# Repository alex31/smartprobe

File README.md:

# SMARTPROBE Pitot3D device

Smartprobe is an autonomous pitot3d tube that is designed to be mounted on a drone.
It records relative wind speed and angles, stores them on sdcard, and stream data on a serial line.

#### *Disclaimer : software was still in alpha stage when the project development was stopped in fall 2021*

## Installation

### The easy way
use the latest binary found under GitHub Releases

### You really want to compile it ?
### Dependencies installation 

>cross compilation and Perl library for the boardGen.pl tool :

``` shell
sudo apt install build-essential gcc-arm-none-eabi gdb-multiarch \
         default-jre libmodern-perl-Perl \
	 libxml-libxml-Perl libfile-which-Perl \
	 dfu-util
	 
sudo cpan -i String/LCSS.pm
```
> to use bmpflash when flashing with a Black Magic Probe or Criquet Probe
``` shell
sudo usermod -a -G dialout $USER
```
### optional : stm32cubemx install from stmicroelectronics website:
https://www.st.com/en/development-tools/stm32cubemx.html
(boardGen.pl script needs xml MCU description files)
If stm32cubemx is not found, a pregenerated board.h is used, you won't be able to modify pin assignation

### clone of GitHub repository and submodules :
``` shell
git clone --recursive https://github.com/alex31/smartprobe.git
cd smartprobe
git submodule update --init --recursive
```

### build firmware in release mode
``` shell
make clean; make BUILD=SIZE
```

### flash firmware in release mode
In dfu mode :
plug micro-USB cable (no need to power supply)
``` shell
make BUILD=SIZE dfuflash

```
In swd mode :
plug swd cable (need to power supply smartprobe)
``` shell
make BUILD=SIZE flash
``` 

## Usage

### µSD Card
It is mandatory to install a micro sd card :
- SD should be formatted with FAT32 or ExFAT filesystem.
- configuration is read from SD
- wind data is stored on the SD
- reading/writing SD can be done
  - offline : SD must be removed
  - online : plug the smartprobe via USB (with SD installed) on a computer, and it will be shown like a USB storage device

### Connector J3 at the back
The Molex connector at the back contains  :  
- power in : Vin should be between 7 and 20 Volts
- bootloader mode switch (connect pin5 with pin6, then power up the smartprobe)
  -bootloader mode is to be used to flash the firmware in the smartprobe
- USB to mount the sdcard as a USB storage device
- UART which can be used for multiple purposes (choice is made in configuration file)

### Parameters
- firmware parameters are read from the SD at start, in a file named ***smartprobe.conf***
- if a file named smartprobe.conf is not found, it will be created, all the fields set at their default value
- the most accurate and up-to-date definitions (with default and range) for each field can be found in source file  
*source/confParameters.hpp*
- here is a list of parameters (details are missing, confParameters.hpp reading is advised)

|Parameter				|                       Description                   	| default 
|-----------				| --------------------------------------------------  	| -----------
|syslog.filename			| name of the file where system events are logged	|syslog
|sensorslog.filename			| name of the file where sensors data are logged	|sensors
|thread.frequency.d_press		| differential pressure sampling frequency  		|100
|thread.frequency.imu			| IMU sampling frequency 				|100
|thread.frequency.stream_console	| frequency of messages on the console			|10
|thread.frequency.transmit_uart		| frequency of messages on serial link			|100
|ahrs.type				| type of AHRS : raw, headless, or complete		|headless_ahrs
|ahrs.output				| ahrs output format : euler or quaternion		|euler
|uart.mode				| no_used or pprz or nmea_in or ubx_in			|pprz
|pprz.message				| pprz msg to stream data : aeroprobe or smartprobe	|aeroprobe
|uart.baud				| Baud rate of the uart in the range 9600..460800	|115200
|canbus.mode				| not yet implemented					|
|canbus.id				| not yet implemented					|
|sensor.barometer.temperatureBias	| temperature bias of the measured exterior air		|-5
|sensor.barometer.lpf			| barometer clock divider    (see LPS33HW datasheet)	|div2
|sensor.barometer.odr			| barometer output data rate (see LPS33HW datasheet)	|50hz
|sensor.d_press.fetched			| diff pressure param fetched : press or press + temp	|P+T
|sensor.d_press.fetchTempFrequency	| diff pressure temp frequency fetching			|1<<
|sensor.imu.accrate			| imu acc fetching rate (see ICM20600 datasheet)	|1khz_bw99
|sensor.imu.gyrorange			| gyro range [250 .. 2000] degrees per seconds		|250_dps
|sensor.imu.accrange			| acc range [2 .. 16] G					|2g
|sensor.imu.estimationLoopDuration_ms	| ahrs calibration duration [10 .. 4000] milliseconds	|500
|airspeed.rho				| estimated (0) or fixed in the range [0.1 .. 2]	|0(force estimation)
|airspeed.calibration.m11		| transformation matrix	from the			|1.15
|airspeed.calibration.m12		| calibration process					|0
|airspeed.calibration.m13		| default values can be used to verify that		|0
|airspeed.calibration.m14		| the smartprobe roughly works, but should not be	|6
|airspeed.calibration.m15		| used to make actual measures				|6
|airspeed.calibration.m21		| 							|0
|airspeed.calibration.m22		| 							|15
|airspeed.calibration.m23		| 							|0
|airspeed.calibration.m24		| 							|0
|airspeed.calibration.m25		| 							|0
|airspeed.calibration.m31		| 							|0
|airspeed.calibration.m32		| 							|0
|airspeed.calibration.m33		| 							|11
|airspeed.calibration.m34		| 							|0
|airspeed.calibration.m35		|		 					|0
|airspeed.calibration.bias.velocity	|bias on air velocity (from calibration)		|0
|airspeed.calibration.bias.alpha	|bias on alfa angle (from calibration)			|0
|airspeed.calibration.bias.beta 	|bias on beta angle (from calibration)			|0
|led.mode				|status or airspeed					|status
|					|							|

## Calibration
Smartprobe should be calibrated in a wind tunnel before use. The calibration matrix values should then be written in the configuration file instead of the default values.

### Calibration procedure :
...TO BE WRITTEN...

## Development tool
there is a SWD connector on the PCB for connecting a debug probe (Black Magic Probe or STlink V2/V3) which permits debugging with gdb and access to a shell console where errors messages are shown.

## troubleshooting
The led color reflect status of operation (see details below). When error occurs, the error details are logged in the syslog file, on the sdcard, and on debug console if a probe is attached to the internal swd+serial connector.

#### error codes :
- blink green : OK
- blink green and orange : sd card file system is dirty, operation will try to continue, but ultimately, there is a need for filesystem check or reformating
- blink orange : sd card mount has failed
- blink green and white : configuration file error
- blink red : hardware fault detected

..
## Ideas for future developments 
- If external componant (autopilot) stream gps positions and heading, wind in a terrestrial reference frame could be calculated on board
- add USB CDC endoint to the existing USB storage endpoint to output serial console shell via USB
- stream UAVCAN messages on the CAN 2.0B interface

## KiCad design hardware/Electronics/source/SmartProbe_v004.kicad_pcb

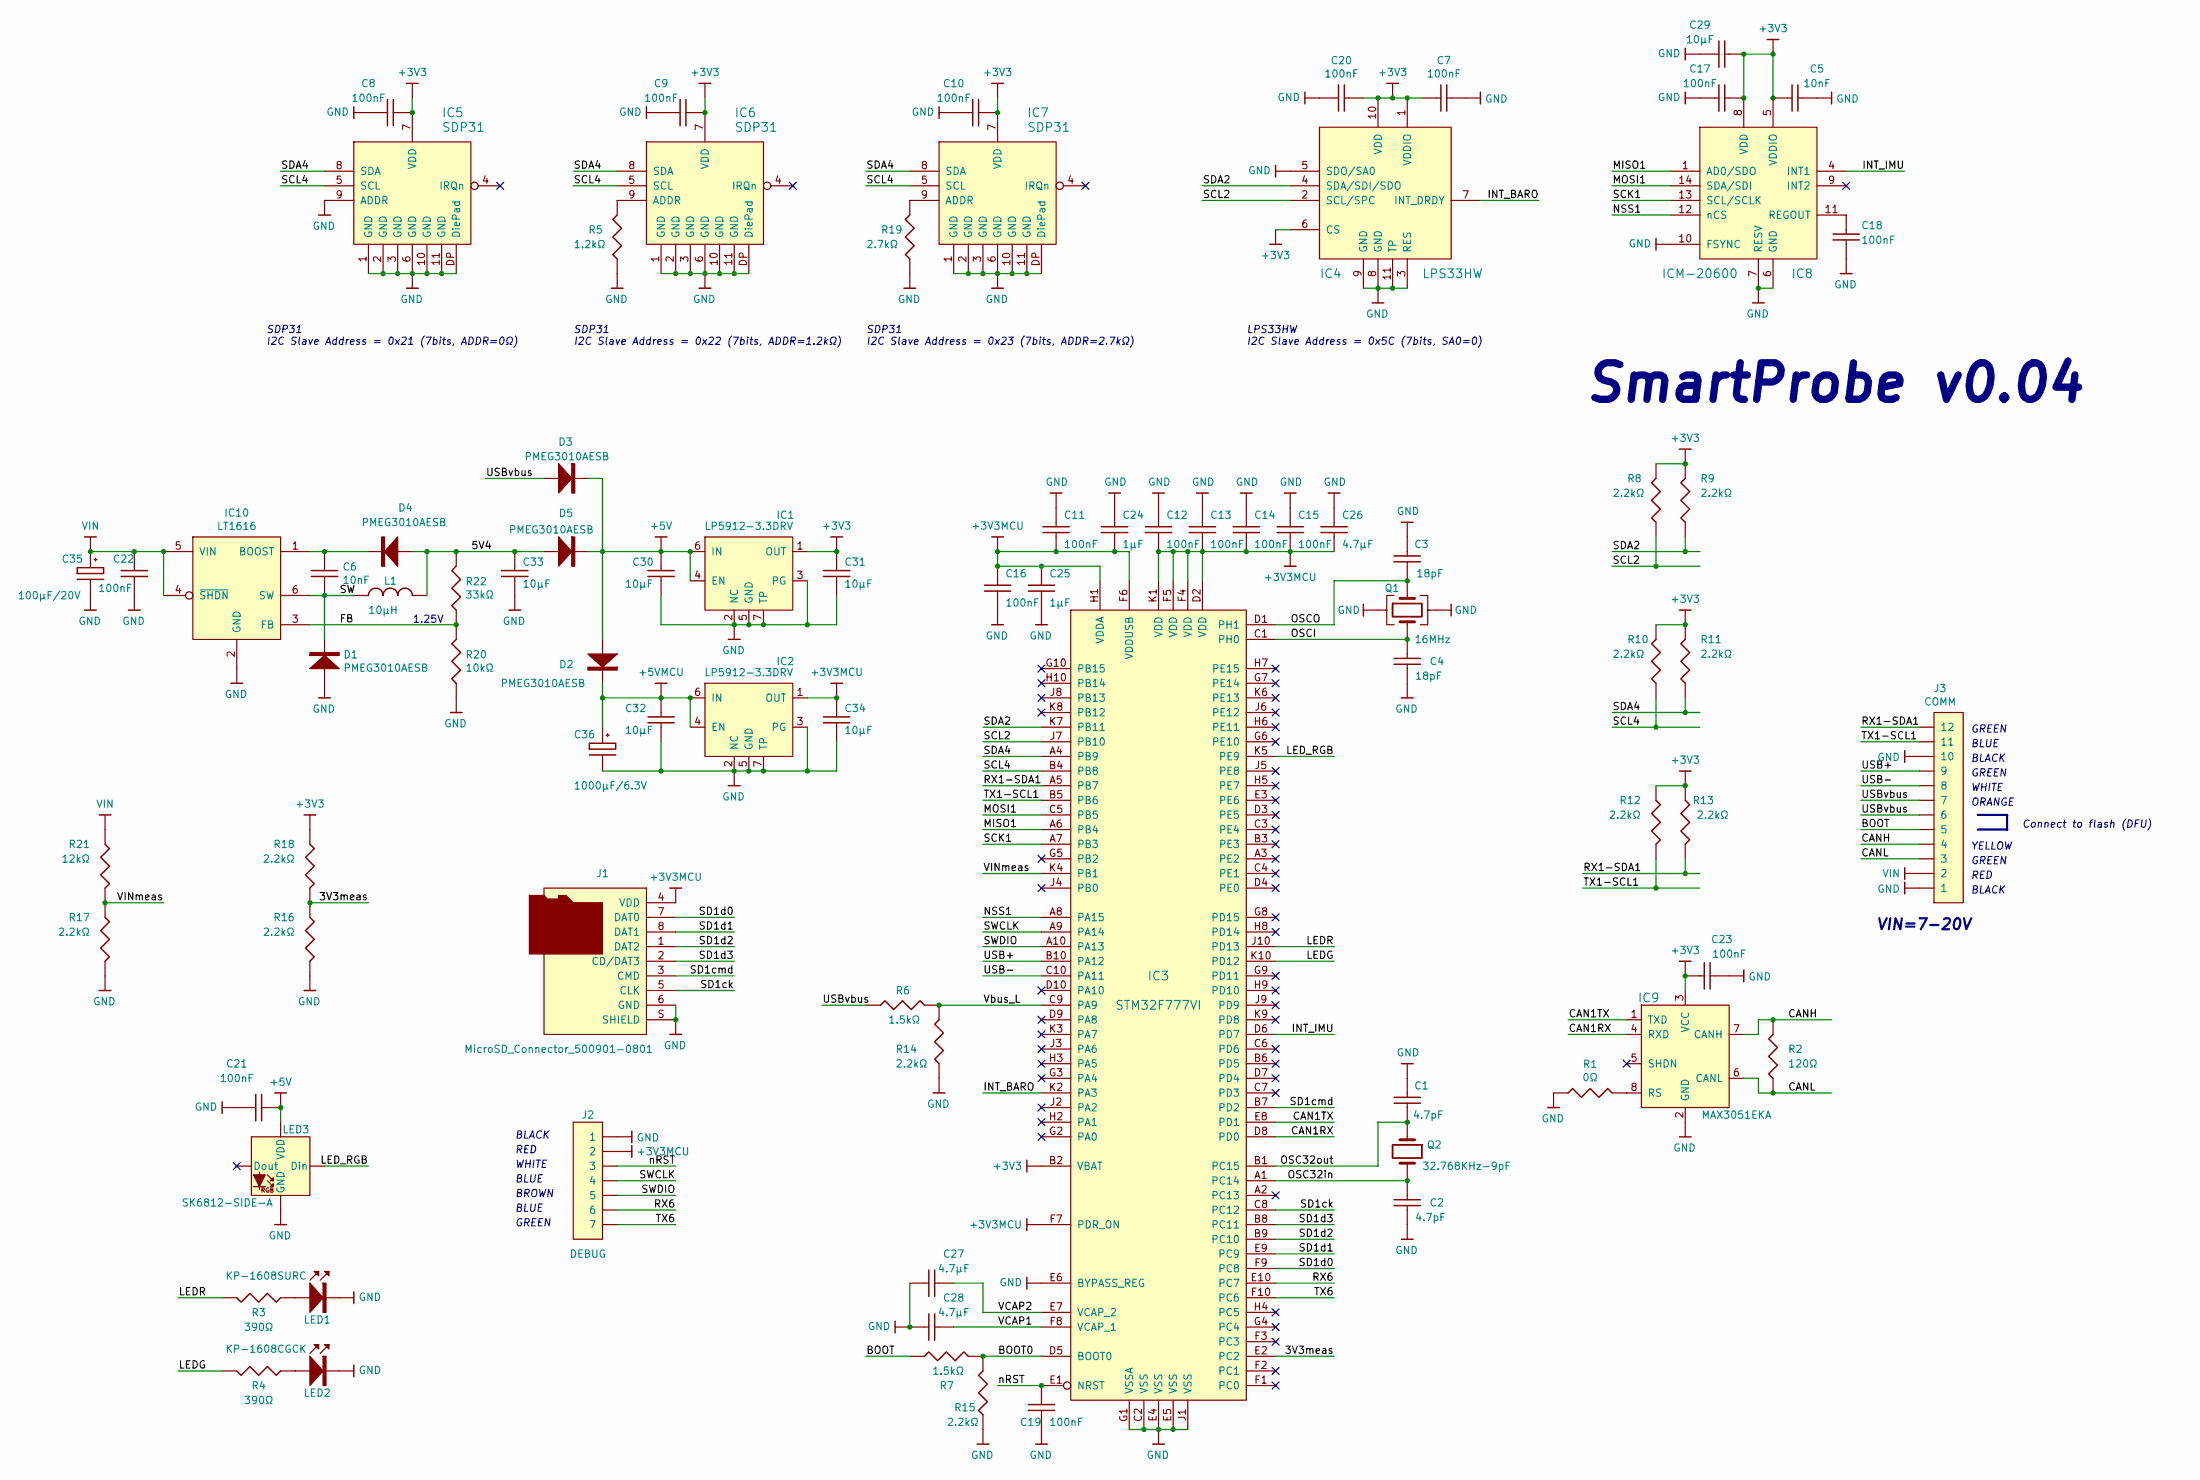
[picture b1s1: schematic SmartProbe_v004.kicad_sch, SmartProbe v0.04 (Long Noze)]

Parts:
C1, C2: 4.7pF; C_0402
C3, C4: 18pF; C_0402
C5, C6: 10nF; C_0402
C7, C8, C9, C10, C11, C12, C13, C14, C15, C16, C17, C18, C19, C20, C21, C22, C23: 100nF; C_0402
C24, C25: 1µF; C_0402
C26, C27, C28: 4.7µF; C_0402
C29, C30, C31, C32, C33, C34: 10µF; C_0603
C35: 100µF/20V; EIA_7343-31
C36: 1000µF/6.3V; EIA_7360-38
D1, D2, D3, D4, D5: PMEG3010AESB
IC1, IC2: LP5912-3.3DRV; LP5912DRV
IC3: STM32F777VI
IC4: LPS33HW
IC5, IC6, IC7: SDP31
IC8: ICM-20600
IC9: MAX3051EKA
IC10: LT1616
J1: MicroSD_Connector_500901-0801; MicroSD_500901-0801
J2: DEBUG; PicoBlade_53261-0771
J3: COMM; PicoBlade_53048-1210
L1: 10µH; VLCF4020T
LED1: KP-1608SURC
LED2: KP-1608CGCK
LED3: SK6812-SIDE-A
Q1: 16MHz; Crystal_8Z
Q2: 32.768KHz-9pF; Crystal_FC-135
R1: 0Ω; R_0402
R2: 120Ω; R_0402
R3, R4: 390Ω; R_0402
R5: 1.2kΩ; R_0402
R6, R7: 1.5kΩ; R_0402
R8, R9, R10, R11, R12, R13, R14, R15, R16, R17, R18: 2.2kΩ; R_0402
R19: 2.7kΩ; R_0402
R20: 10kΩ; R_0402
R21: 12kΩ; R_0402
R22: 33kΩ; R_0402

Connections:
+3V3: C5.2, C7.2, C8.1, C9.1, C10.1, C17.1, C20.1, C23.2, C29.1, C31.1, IC1.1 (OUT), IC3.B2 (VBAT), IC4.1 (VDDIO), IC4.6 (CS), IC4.10 (VDD), IC5.7 (VDD), IC6.7 (VDD), IC7.7 (VDD), IC8.5 (VDDIO), IC8.8 (VDD), IC9.3 (VCC), R8.1, R9.1, R10.1, R11.1, R12.1, R13.1, R18.1
+3V3MCU: C11.2, C12.2, C13.2, C14.2, C15.2, C16.1, C24.2, C25.1, C26.2, C34.1, IC2.1 (OUT), IC3.D2 (VDD), IC3.F4 (VDD), IC3.F5 (VDD), IC3.F6 (VDDUSB), IC3.F7 (PDR_ON), IC3.H1 (VDDA), IC3.K1 (VDD), J1.4 (VDD), J2.2
+5V: C21.1, C30.1, D2.2 (A), D3.1 (K), D5.1 (K), IC1.4 (EN), IC1.6 (IN), LED3.2 (VDD)
+5VMCU: C32.1, C36.1, D2.1 (K), IC2.4 (EN), IC2.6 (IN)
/3V3meas: IC3.E2 (PC2), R16.1, R18.2
/5V4: C33.1, D4.2 (A), D5.2 (A), L1.2, R22.1
/BOOT: J3.5, R7.2
/BOOT0: IC3.D5 (BOOT0), R7.1, R15.1
/CAN1RX: IC3.D8 (PD0), IC9.4 (RXD)
/CAN1TX: IC3.E8 (PD1), IC9.1 (TXD)
/CANH: IC9.7 (CANH), J3.4, R2.1
/CANL: IC9.6 (CANL), J3.3, R2.2
/FB: IC10.3 (FB), R20.1, R22.2
/INT_BARO: IC3.K2 (PA3), IC4.7 (INT_DRDY)
/INT_IMU: IC3.D6 (PD7), IC8.4 (INT1)
/LEDG: IC3.K10 (PD12), R4.1
/LEDR: IC3.J10 (PD13), R3.1
/LED_RGB: IC3.K5 (PE9), LED3.1 (Din)
/MISO1: IC3.A6 (PB4), IC8.1 (AD0/SDO)
/MOSI1: IC3.C5 (PB5), IC8.14 (SDA/SDI)
/NSS1: IC3.A8 (PA15), IC8.12 (nCS)
/OSC32in: C2.2, IC3.A1 (PC14), Q2.2
/OSC32out: C1.2, IC3.B1 (PC15), Q2.1
/OSCI: C4.2, IC3.C1 (PH0), Q1.3
/OSCO: C3.2, IC3.D1 (PH1), Q1.1
/RX1-SDA1: IC3.A5 (PB7), J3.12, R13.2
/RX6: IC3.E10 (PC7), J2.6
/SCK1: IC3.A7 (PB3), IC8.13 (SCL/SCLK)
/SCL2: IC3.J7 (PB10), IC4.2 (SCL/SPC), R8.2
/SCL4: IC3.B4 (PB8), IC5.5 (SCL), IC6.5 (SCL), IC7.5 (SCL), R10.2
/SD1ck: IC3.C8 (PC12), J1.5 (CLK)
/SD1cmd: IC3.B7 (PD2), J1.3 (CMD)
/SD1d0: IC3.F9 (PC8), J1.7 (DAT0)
/SD1d1: IC3.E9 (PC9), J1.8 (DAT1)
/SD1d2: IC3.B9 (PC10), J1.1 (DAT2)
/SD1d3: IC3.B8 (PC11), J1.2 (CD/DAT3)
/SDA2: IC3.K7 (PB11), IC4.4 (SDA/SDI/SDO), R9.2
/SDA4: IC3.A4 (PB9), IC5.8 (SDA), IC6.8 (SDA), IC7.8 (SDA), R11.2
/SW: C6.2, D1.1 (K), IC10.6 (SW), L1.1
/SWCLK: IC3.A9 (PA14), J2.4
/SWDIO: IC3.A10 (PA13), J2.5
/TX1-SCL1: IC3.B5 (PB6), J3.11, R12.2
/TX6: IC3.F10 (PC6), J2.7
/USB+: IC3.B10 (PA12), J3.9
/USB-: IC3.C10 (PA11), J3.8
/USBvbus: D3.2 (A), J3.6, J3.7, R6.2
/VCAP1: C28.1, IC3.F8 (VCAP_1)
/VCAP2: C27.1, IC3.E7 (VCAP_2)
/VINmeas: IC3.K4 (PB1), R17.1, R21.2
/Vbus_L: IC3.C9 (PA9), R6.1, R14.1
/nRST: C19.1, IC3.E1 (NRST), J2.3
GND: C1.1, C2.1, C3.1, C4.1, C5.1, C7.1, C8.2, C9.2, C10.2, C11.1, C12.1, C13.1, C14.1, C15.1, C16.2, C17.2, C18.2, C19.2, C20.2, C21.2, C22.2, C23.1, C24.1, C25.2, C26.1, C27.2, C28.2, C29.2, C30.2, C31.2, C32.2, C33.2, C34.2, C35.2, C36.2, D1.2 (A), IC1.2 (NC), IC1.3 (PG), IC1.5 (GND), IC1.7 (TP), IC2.2 (NC), IC2.3 (PG), IC2.5 (GND), IC2.7 (TP), IC3.C2 (VSS), IC3.E4 (VSS), IC3.E5 (VSS), IC3.E6 (BYPASS_REG), IC3.G1 (VSSA), IC3.J1 (VSS), IC4.3 (RES), IC4.5 (SDO/SA0), IC4.8 (GND), IC4.9 (GND), IC4.11 (TP), IC5.1 (GND), IC5.2 (GND), IC5.3 (GND), IC5.6 (GND), IC5.9 (ADDR), IC5.10 (GND), IC5.11 (GND), IC5.DP (DiePad), IC6.1 (GND), IC6.2 (GND), IC6.3 (GND), IC6.6 (GND), IC6.10 (GND), IC6.11 (GND), IC6.DP (DiePad), IC7.1 (GND), IC7.2 (GND), IC7.3 (GND), IC7.6 (GND), IC7.10 (GND), IC7.11 (GND), IC7.DP (DiePad), IC8.6 (GND), IC8.7 (RESV), IC8.10 (FSYNC), IC9.2 (GND), IC10.2 (GND), J1.6 (GND), J1.S (SHIELD), J2.1, J3.1, J3.10, LED1.1 (K), LED2.1 (K), LED3.4 (GND), Q1.2, Q1.4, R1.2, R5.2, R14.2, R15.2, R16.2, R17.2, R19.2, R20.2
unnamed: C6.1, D4.1 (K), IC10.1 (BOOST)
unnamed: C18.1, IC8.11 (REGOUT)
unnamed: IC6.9 (ADDR), R5.1
unnamed: IC7.9 (ADDR), R19.1
unnamed: IC9.8 (RS), R1.1
unnamed: LED1.2 (A), R3.2
unnamed: LED2.2 (A), R4.2
VIN: C22.1, C35.1, IC10.4 (~SHDN), IC10.5 (VIN), J3.2, R21.1

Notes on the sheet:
GREEN
BLACK
1.25V
ORANGE
BROWN
BLUE
WHITE
SDP31 I2C Slave Address = 0x22 (7bits, ADDR=1.2kΩ)
SDP31 I2C Slave Address = 0x21 (7bits, ADDR=0Ω)
VIN=7-20V
YELLOW
RED
LPS33HW I2C Slave Address = 0x5C (7bits, SA0=0)
SmartProbe v0.04
Connect to flash (DFU)
SDP31 I2C Slave Address = 0x23 (7bits, ADDR=2.7kΩ)

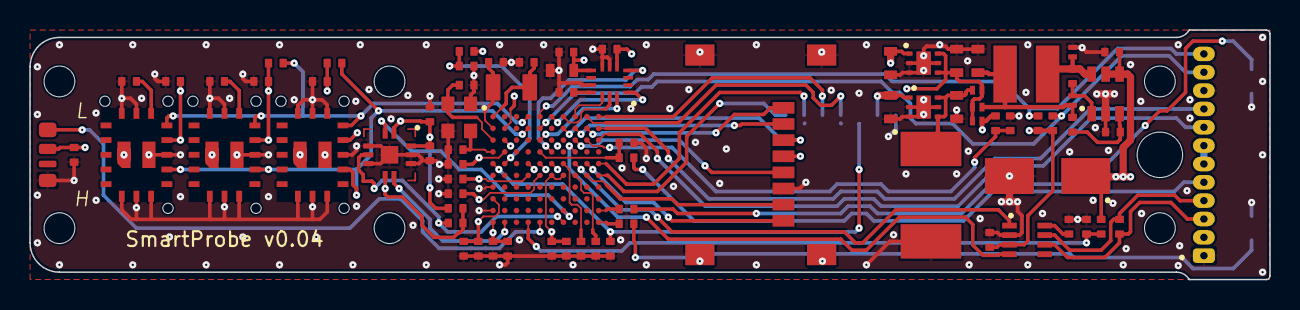
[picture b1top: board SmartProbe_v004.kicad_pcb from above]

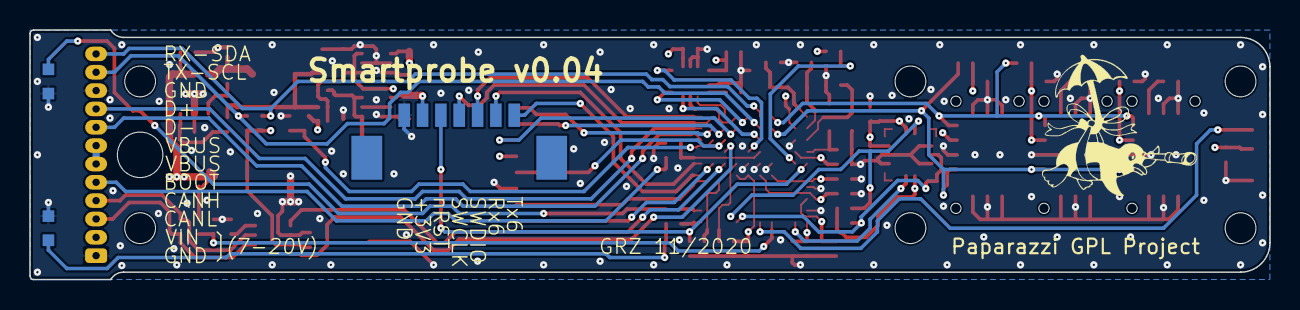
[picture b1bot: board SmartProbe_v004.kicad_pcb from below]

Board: 4 copper layers, 84.5 x 17.0 mm, 82 parts (3 on the bottom side), 60 nets.

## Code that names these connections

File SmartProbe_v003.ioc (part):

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Mcu.Name=STM32F777VIHx
Mcu.Package=TFBGA100
Mcu.UserName=STM32F777VIHx
PA11.GPIOParameters=GPIO_Label
PA11.GPIO_Label=USB-
PA11.Mode=Device_Only
PA11.Signal=USB_OTG_FS_DM
PA12.GPIOParameters=GPIO_Label
PA12.GPIO_Label=USB+
PA12.Mode=Device_Only
PA12.Signal=USB_OTG_FS_DP
PA13.GPIOParameters=GPIO_Label
PA13.GPIO_Label=SWDIO
PA13.Mode=Serial_Wire
PA13.Signal=SYS_JTMS-SWDIO
PA14.GPIOParameters=GPIO_Label
PA14.GPIO_Label=SWCLK
PA14.Mode=Serial_Wire
PA14.Signal=SYS_JTCK-SWCLK
PA15.GPIOParameters=GPIO_Label
PA15.GPIO_Label=NSS1
PA15.Mode=NSS_Signal_Hard_Output
PA15.Signal=SPI1_NSS
PA3.GPIOParameters=GPIO_Label
PA3.GPIO_Label=INT_BARO
PA3.Signal=GPIO_Input
PA9.GPIOParameters=GPIO_Label
PA9.GPIO_Label=Vbus
PA9.Mode=Activate_VBUS
PA9.Signal=USB_OTG_FS_VBUS
PB1.GPIOParameters=GPIO_Label
PB1.GPIO_Label=VINmeas
PB1.Signal=ADCx_IN9
PB10.GPIOParameters=GPIO_Label
PB10.GPIO_Label=SCL2
PB10.Mode=I2C
PB10.Signal=I2C2_SCL
PB11.GPIOParameters=GPIO_Label
PB11.GPIO_Label=SDA2
PB11.Mode=I2C
PB11.Signal=I2C2_SDA
PB3.GPIOParameters=GPIO_Label
PB3.GPIO_Label=SCK1
PB3.Mode=Full_Duplex_Master
PB3.Signal=SPI1_SCK
PB4.GPIOParameters=GPIO_Label
PB4.GPIO_Label=MISO1
PB4.Mode=Full_Duplex_Master
PB4.Signal=SPI1_MISO
PB5.GPIOParameters=GPIO_Label
PB5.GPIO_Label=MOSI1
PB5.Mode=Full_Duplex_Master
PB5.Signal=SPI1_MOSI
PB6.GPIOParameters=GPIO_Label
PB6.GPIO_Label=TX1-SCL1
PB6.Mode=Asynchronous
PB6.Signal=USART1_TX
PB7.GPIOParameters=GPIO_Label
PB7.GPIO_Label=RX1-SDA1
PB7.Mode=Asynchronous
PB7.Signal=USART1_RX
PB8.GPIOParameters=GPIO_Label
PB8.GPIO_Label=SCL4
PB8.Mode=I2C
PB8.Signal=I2C4_SCL
PB9.GPIOParameters=GPIO_Label
PB9.GPIO_Label=SDA4
PB9.Mode=I2C
PB9.Signal=I2C4_SDA
PC10.GPIOParameters=GPIO_Label
PC10.GPIO_Label=SD1d2
PC10.Mode=SD_4_bits_Wide_bus
PC10.Signal=SDMMC1_D2
PC11.GPIOParameters=GPIO_Label
PC11.GPIO_Label=SD1d3
PC11.Mode=SD_4_bits_Wide_bus
PC11.Signal=SDMMC1_D3
PC12.GPIOParameters=GPIO_Label
PC12.GPIO_Label=SD1ck
PC12.Mode=SD_4_bits_Wide_bus
PC12.Signal=SDMMC1_CK
PC14/OSC32_IN.GPIOParameters=GPIO_Label
PC14/OSC32_IN.GPIO_Label=OSC32IN
PC14/OSC32_IN.Mode=LSE-External-Oscillator
PC14/OSC32_IN.Signal=RCC_OSC32_IN
PC15/OSC32_OUT.GPIOParameters=GPIO_Label
PC15/OSC32_OUT.GPIO_Label=OSC32OUT
PC15/OSC32_OUT.Mode=LSE-External-Oscillator
PC15/OSC32_OUT.Signal=RCC_OSC32_OUT
PC2.GPIOParameters=GPIO_Label
PC2.GPIO_Label=_3V3meas
PC2.Signal=ADCx_IN12
PC6.GPIOParameters=GPIO_Label
PC6.GPIO_Label=TX6
PC6.Mode=Asynchronous
PC6.Signal=USART6_TX
PC7.GPIOParameters=GPIO_Label
PC7.GPIO_Label=RX6
PC7.Mode=Asynchronous
PC7.Signal=USART6_RX
PC8.GPIOParameters=GPIO_Label
PC8.GPIO_Label=SD1d0
PC8.Mode=SD_4_bits_Wide_bus
PC8.Signal=SDMMC1_D0
PC9.GPIOParameters=GPIO_Label
PC9.GPIO_Label=SD1d1
PC9.Mode=SD_4_bits_Wide_bus
PC9.Signal=SDMMC1_D1
PD0.GPIOParameters=GPIO_Label
PD0.GPIO_Label=CAN1RX
PD0.Mode=Master
PD0.Signal=CAN1_RX
PD1.GPIOParameters=GPIO_Label
PD1.GPIO_Label=CAN1TTX
PD1.Mode=Master
PD1.Signal=CAN1_TX
PD12.GPIOParameters=GPIO_Label
PD12.GPIO_Label=LEDG
PD12.Signal=GPIO_Output
PD13.GPIOParameters=GPIO_Label
PD13.GPIO_Label=LEDR
PD13.Signal=GPIO_Output
PD2.GPIOParameters=GPIO_Label
PD2.GPIO_Label=SD1cmd
PD2.Mode=SD_4_bits_Wide_bus
PD2.Signal=SDMMC1_CMD
PD7.GPIOParameters=GPIO_Label
PD7.GPIO_Label=INT_IMU
PD7.Signal=GPIO_Input
PE9.GPIOParameters=GPIO_Label
PE9.GPIO_Label=LED_RGB
PE9.Signal=S_TIM1_CH1
PH0/OSC_IN.Mode=HSE-External-Oscillator
PH0/OSC_IN.Signal=RCC_OSC_IN
PH1/OSC_OUT.Mode=HSE-External-Oscillator
PH1/OSC_OUT.Signal=RCC_OSC_OUT
RCC.HSE_VALUE=25000000
board=custom

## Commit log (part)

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2019-10-25 only basic shell in c++
2019-10-25 smartprobe : board.cfg written for specific hardware
2019-10-30 remove globalVar
2019-10-30 modify Makefile to add CTRE, FROZEN and ETL header only libraries
2019-11-05 use fpu
2019-11-08 add fatfs, tlsf
2019-11-15 add sdLog
2019-11-15 add i2cMaster, spi; fix dma streams
2019-11-15 add baro thread
2019-11-15 add and abstaction of a working class
2019-11-16 add join, terminate, and destructor
2019-11-18 fix thread abstaction, before baro using thread abstaction, tested ok on devboardm767
2019-11-18 add missing files
2019-11-19 baro use thread abstraction
2019-11-19 add adc, apply CRTP to worker template class to avoid thread handle sharing
2019-11-19 add imu, not tested
2019-11-20 add sdcard, tested on devboardm767 ok
2019-11-20 all peripherals tested ok on smartprobe
2019-11-21 use reworked sdLog.c whith fixed autoflush period, works ok without dirty bit on few tries. Should be teste more thoroughly
2019-11-21 fix incorrect values of the resistors used in the power supply voltage divider
2019-11-25 add blackboard.hpp
2019-11-25 add blackBoard test files
2019-11-25 baro, adc and differential pressure emit event
2019-11-25 fix main trhead stack size in optimized compilation
2019-11-26 imu also send event, so now all sensors send events
2019-11-26 update todolist
2019-11-26 add usb_storage
2019-11-27 workerClass : avoid virtual inderection in loop using CRTP
2019-11-27 indicate that thread run only once using noreturn kw
2019-11-27 change led1 led2 by led_green led_red
2019-11-27 use syslog instead of debug trace, write git revision and other useful info @ syslog start
2019-11-27 log all sensors data @100 hz on the sdcard
2019-11-27 fix source event : dpif instead of baro
2019-11-27 fix event was sent for each of the 3 dp sensors, but only one event is expected
2019-11-28 add a rough program to display sensors output
2019-11-28 refresh binaries
2019-11-28 clean flow control in main.cpp, simplify shell close command
2019-11-28 fix stopAllPeripherals, called in case of power supply stop. it made chibios chSysHalt, and no sdcard clean close was done
2019-12-03 4.4v threshold for tests before dynamic threshold
2019-12-03 dynamic shutdown threashold voltage (not tested)
2019-12-04 fix app code because of chibios fix #1060 to restore usb_storage; fix VSS initial calculation
2019-12-12 generate binary
2019-12-12 portage from linux to MCU fails because of embedded libc++ limitation : try to switch to etl
2019-12-13 initial portage completed whithout the need to switch to ETL
2019-12-14 read / write conf file code written, not tested
2019-12-14 begin use of conf parameters
2019-12-14 first actual use of conf parameters
2019-12-14 use conf parameter for sensors initialisation parameters
2019-12-17 raise dynamic memory pool size, raise threads stack size, still memory problem with certain level of optimisation, namely -Og
2019-12-17 fix dynamic string possibily of failure
2019-12-17 replace some string_view by std::string to avoid memory corruption
2019-12-17 modity makefile to permit so select build type (DEBUG, SIZE, SPEED) on command line
2019-12-17 remove ETL : F7 don't lack memory, and we need dynamic allocation, so we can use STL for all
2019-12-17 test and reformat syslog messages generated by configuration file reading : tested OK
2019-12-18 print associated alias for default value and syslog message, update todo.txt
2019-12-19 integrate ahrs, still need to log euler angles to sdcard
2019-12-20 log euler angles to sdcard, with a configuration parameter to choose between raw imu and ahrs estimated euler angles
2019-12-21 calculate relative wind vector : big concern about calibration matrix orientation numpy vs eigen
2019-12-21 use eigen operator[] to get vector element instead operator ()
2019-12-21 estimate rho from baro, or use std value given in conf file
2019-12-22 raise d_press to 2khz (need new sdp3x), replace fast inv sqrt by std use of FPU
2019-12-22 test is a line is too long for the internal buffer to avoid a crash
2019-12-22 add parameters for SDP3X : fetch pressure and temperature, temperature getch frequency relative to pressure
2019-12-23 crashes orginin is : newlib's *s*printf class of function are not reentrant (libc one are, so man say it's reentrant) : I commit a temporary fix using newlib _*s*printf_r class of function, but the r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
2019-12-23 add a copy of the configuration file on the sdcard smartprobe.conf, update todo.txt
2019-12-23 revert Makefile debug build to -Og
2019-12-23 add binary with their new name
2019-12-23 fix potential problems : no reentrancy of newlib sprintf, protect (mutex) configuration dictionary access, preallocate std::string
2019-12-23 more precise timestamp when aquisition frequency is over >= 100hz
2019-12-24 fix va_list bug when no trace, fix no serialdatastrem when no trace
2019-12-25 make line parsing more robust : ctre sometime crash, so comment remove is done by strtok prior to regexp matching
2019-12-25 revert to STM32F777VIHx (part in board.cfg)
2020-01-08 make all internal IMU angle be in radian, degree only used for display and ascii log. 3d wind calculus stay in degrees for now
2020-01-08 detect swdio activity, and close cleanly sdcard before entering swdio mode; put fatfs in pedantic mode : will not mount FS with dirty bit neither cluster incoherency
2020-01-08 fix swdio action after deteection
2020-01-22 in the streamed data (low frequency), mean attitude and air vector instead of taking one sample
2020-02-05 display fixes in spGui.pl
2020-02-06 add capacity to send aeroprobe message to pprz via uart (not tested)
2020-02-07 add capacity to get pprz message from uart (not tested)
2020-02-07 launch uart receive thread in main.cpp when mode is PPRZ_IN_OUT
2020-02-07 generate binaries
2020-02-14 emit event on pprz message, implement itow to rtcdate
2020-02-14 change file and class name
2020-02-14 change file and class name (part 2)
2020-02-14 add pprzlink encoder decoder files
2020-02-20 remove warning about wind velocity calculation : tested OK
2020-02-26 still bugs in reading conf files
2020-02-26 add a comment sign (#) after value when generating conf file
2020-02-26 do no run showBB when uart is in link mode
2020-02-27 add warning and checks at compilation, modify sources according to new rules
2020-02-27 fix serial driver initialisation
2020-02-27 remove test code for ppzr link
2020-02-28 fix method to wait for uart initialisation
2020-02-28 add code to sync RTC with GPS (not tested)
2020-03-16 add gps nmea input (not finished, lacks pubx 00
2020-03-18 create unit test for nmeaFrame modification
2020-03-19 add and test nmea pubx,yy message reception, tested OK
2020-03-19 remove binding to GGA and VTG nmea message which are no more needed when using PUBX,00
2020-03-19 fix lla to utm conversion
2020-03-26 UBX : discard faster non ubx or non topic message, syslog quantity of discard garbage
2020-03-26 add configuration value : canbus id in prevision of installing many SP on a plane
2020-03-26 fix uwb swallow bug which lead to read 0 bytes on a channel (chibios trapped error)
2020-03-26 add schematics of V003 version of the board
2020-03-27 update todo
2020-03-27 use new pprzlink api with user data
2020-03-30 fix ubx event bug
2020-03-30 sensorlog (TSV format) gps data if avalaible
2020-03-30 add etl profile since we use it again
2020-04-01 remove stuff in mail
2020-04-01 trace uart speed is not anymore in configuration file, add non compound statement macro since the compund one trigger a strange bug
2020-04-01 fix order of initialisation : get log name from configuration file
2020-04-02 fix chronology problem at start, move constants to hardwareConf.hpp
2020-04-02 simplify main, enable MPU based stack overflow check
2020-04-02 fix a very serious bug in dynamic memory management : operateur new and delete was not redefinded in all copilation units
2020-04-08 add binary log option and tool to convert offline binary logs to tsv logs
2020-04-08 add 3d rendering of smartprobe
2020-04-15 raise main thread stack size
2020-04-27 we do not use pwmd9
2020-05-11 make g++10 happy
2020-06-02 fix printf format errors
2020-06-09 begin replacement of sdLog library by sdLiteLog (not finished)
2020-06-12 sdLiteLog finish replacement of sdLog library by sdLiteLog, tested, seems OK, need more tests
2020-07-01 use C++ fmt library instead of C stdio sprintf : speed gain of 60%
2020-07-01 use of sdLiteLog : buffer size is centralised in hardwareConf.hpp
2020-07-01 fix typo in logical test
2020-09-02 portage to v003 : led in the noose, voltage from battery no from 5V regulator
2020-09-03 port to chibios 20.03
2020-09-03 add some submodules, needs a lot more
2020-09-08 fix µsecond calculus truncated to 32 bits : was wrapping after 1 hour and 10 minutes
2020-09-08 time in binary and text log are now expressed in seconds, not milliseconds
2020-09-08 fix hard hangs at first start after sdcard reformat
2020-09-09 add LTO in Makefile
2020-09-09 power supply is not 5V anymore, so change the label
2020-09-09 launch showBB thread only whenh TRACE is defined
2020-09-17 sample 4 adc channels
2020-09-17 repair wronf git command
2020-09-17 do no track generated file board.h
2020-09-18 smartled : add a starting state where we cycle over Hue values
2020-09-18 add led code for swdio mode, detect and wait
2020-09-18 periodicly check thread stack occupancy, internal voltage, core temp and log abnormal values
2020-09-22 use INT1 pin of IMU TDK20600 to trigger acquisition
2020-09-23 put eigen in a submodule
2020-09-23 put all depencies as submodules
2020-09-23 add file
2020-09-23 add README.md
2020-09-23 add Makefile entry to flash in dfu mode
2020-09-23 fix typos in README.md
2020-09-23 begin to fix bad behaviour chan compiled in RELEASE mode
2020-09-24 --specs=nano.specs is not compatible with complex c++ data scheme, removing it
2020-09-24 Makefile take care of swdio detection when flashing
2020-09-24 modify color code for nose led
2020-09-24 - smartLed is not a library component anymore - version number of syslog and sensorlog are now synchronized
2020-09-24 minor reorganisation of syslog first status lines
2020-11-18 fix a bug found by murat : relAirSpeedSum was not cleared at end of time window
2020-11-18 for now attitude is not transmitted on pprz link, so avoid unnecessary calculus
2020-11-18 fix long constant (20 digits) make parser to segfault, fix no associated led error code to sdcard format not recognised
2020-11-20 lower voltage by element threshold to avoid smartprobe unexpected shutdown during flight with nearly empty battery
2020-11-23 disable SDMMC PWRSAV feature
2021-05-05 submodule update for chibios 20.3
2021-05-05 change internal thread parameter name to follow chibios API change
2021-05-25 update submodules and follow api changes
2021-05-26 add a conf parameter to choose between aeroprobe and smartprobe message on the pprzlink channel
2021-05-26 add possibility to generate smartprobe message instead of aeroprobe
2021-05-26 °add tas parameter to the streamed pprz message °short flash the noose led after init to lower heat generation
2021-05-26 use tickless scheduler @20khz, disable PROFILING and use STATISTICS instead
2021-05-26 begin to use window average : no good values yet
2021-05-26 window average static pressure and temperature to calculate rho
2021-05-26 remove debug trace
2021-05-27 add feature eluer or quaternion choice, only effective on serial link, not sdcard for now
2021-06-01 update ext submodules dependencies
2021-06-01 gcc 11 comptability changes
2021-06-01 gcc 11 comptability changes when using lto
2021-09-05 fix compilation mode in makefile, change mix/max for messages frequency
2021-09-23 add code to make led color and intensity change with relative air speed tas and alpha : does not seems to start
2021-09-24 fix led color and intensity change with relative air speed tas and alpha
2021-09-27 add tools to decode / display pprz smartprobe (id=60) message
2023-08-04 port from chibios 20.3 to chibios 21.11.4 : still need to update submodules after tests
2023-08-04 update submodules
2024-11-28 port to gcc 14.2

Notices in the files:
hardware/Electronics/source/SmartProbe_v004.kicad_pcb:
Paparazzi GPL Project
hardware/Electronics/source/SmartProbe_v004.kicad_sch:
ENAC Paparazzi GPL Project
